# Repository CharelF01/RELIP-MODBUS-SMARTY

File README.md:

# RELIP
This project was done in the scope of the BTS-Internet of Things in the Lycée des Arts et Métiers Luxembourg with the help of Bâtiment Public Luxembourg.
The Real Life Project's objective was to make a functioning device that decrypts the data from the luxembourgish smart electrical meter and sends it out via ModBus TCP and/or RTU.

Mark received on Project: 17.5/20

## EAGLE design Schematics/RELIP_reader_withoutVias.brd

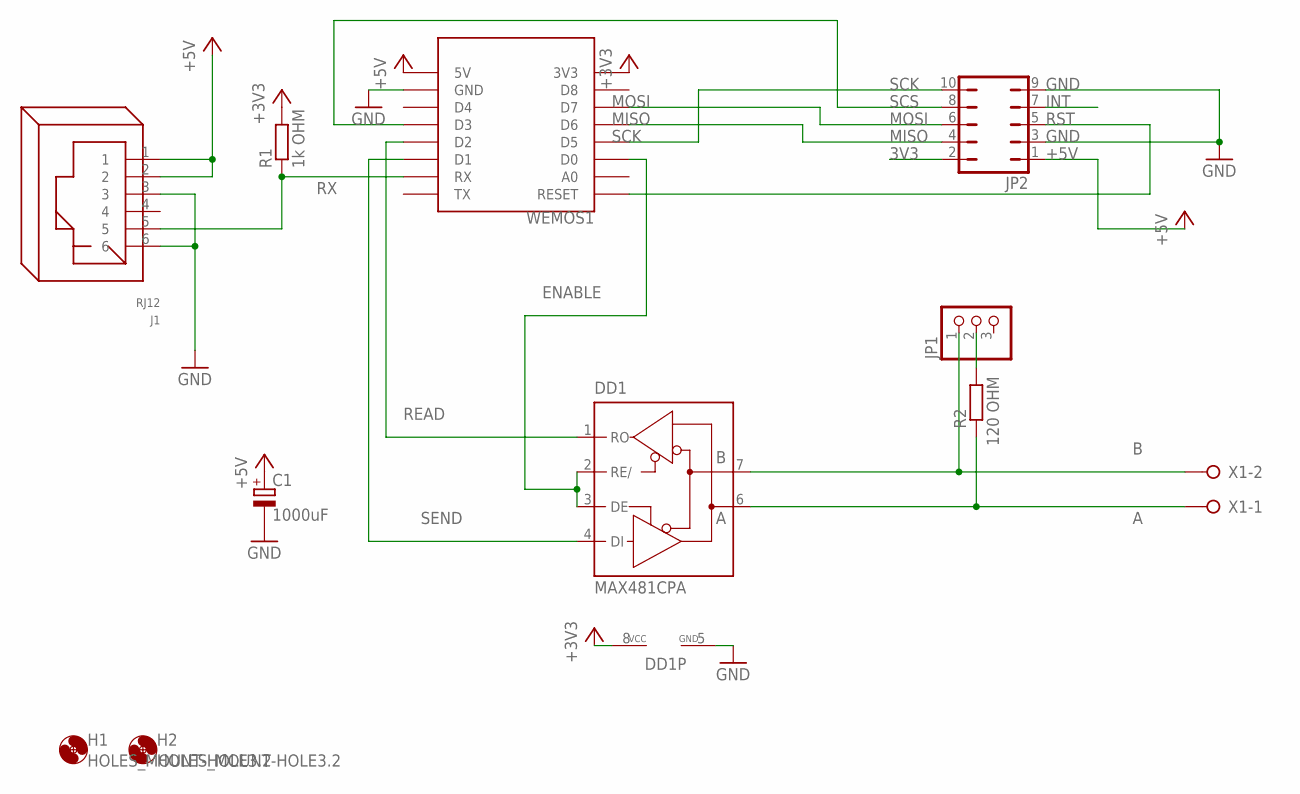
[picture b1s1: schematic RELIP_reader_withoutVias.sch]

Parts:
C1: 1000uF; E3,5-8
DD1: MAX481CPA; DIL08
H1, H2: HOLES_MOUNT-HOLE3.2; HOLES_3,2
J1: RJ12
JP1: PINHEAD_PINHD-1X3; PINHEAD_1X03
JP2: JP5Q
R1: 1k OHM; RCL_0207/12
R2: 120 OHM; RCL_0207/12
WEMOS1: WEMOS-D1-MINI
X1: W237-02P; W237-132

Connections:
3V3: JP2.2
+3V3: DD1.8 (VCC), R1.2, WEMOS1.3V3
+5V: C1.+, J1.1, J1.2, JP2.1, WEMOS1.5V
A: DD1.6 (A), R2.1, X1.1
B: DD1.7 (B), JP1.1, X1.2
ENABLE: DD1.2 (RE/), DD1.3 (DE), WEMOS1.D0
GND: C1.-, DD1.5 (GND), J1.3, J1.6, JP2.3, JP2.9, WEMOS1.GND
INT: JP2.7
MISO: JP2.4, WEMOS1.D6
MOSI: JP2.6, WEMOS1.D7
unnamed: JP1.2, R2.2
READ: DD1.1 (RO), WEMOS1.D2
RST: JP2.5, WEMOS1.RESET
RX: J1.5, R1.1, WEMOS1.RX
SCK: JP2.10, WEMOS1.D5
SCS: JP2.8, WEMOS1.D3
SEND: DD1.4 (DI), WEMOS1.D1

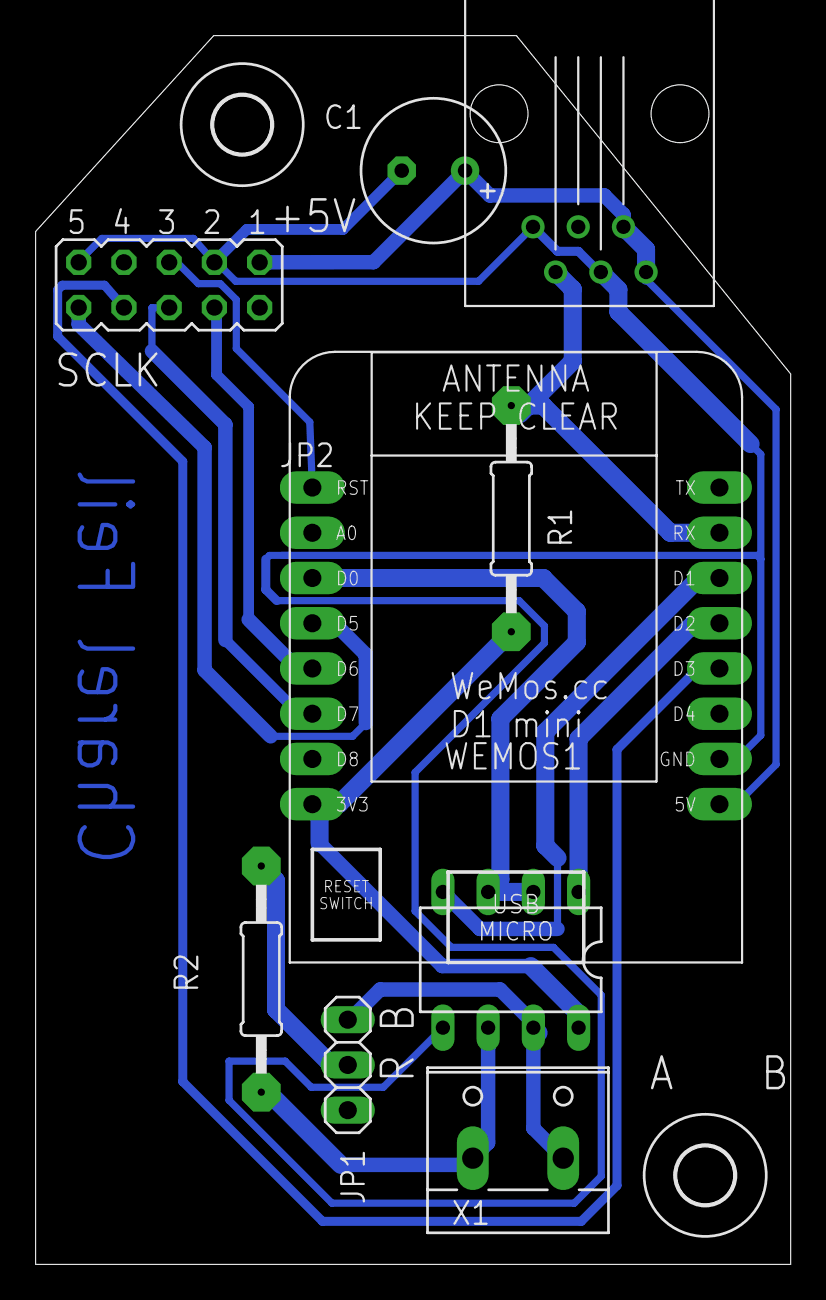
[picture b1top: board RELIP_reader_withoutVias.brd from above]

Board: 2 copper layers, 42.4 x 69.0 mm, 11 parts (0 on the bottom side), 15 nets.

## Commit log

2023-04-04 upload
2023-04-05 Rename LICENsE.md to LICENSE.md
2023-05-25 add Mark
